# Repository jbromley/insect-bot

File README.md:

Insect Bot README
=================

This repository contains code and other documents for an insect bot based on
the bot in chapter 4 of [Make: Arduino Bots and Gadgets: Six Embedded
Projects with Open Source Hardware and
Software](http://www.amazon.com/Make-Embedded-Projects-Hardware-Discovery/dp/1449389716/ref=sr_1_1?ie=UTF8&qid=1329163647&sr=8-1).

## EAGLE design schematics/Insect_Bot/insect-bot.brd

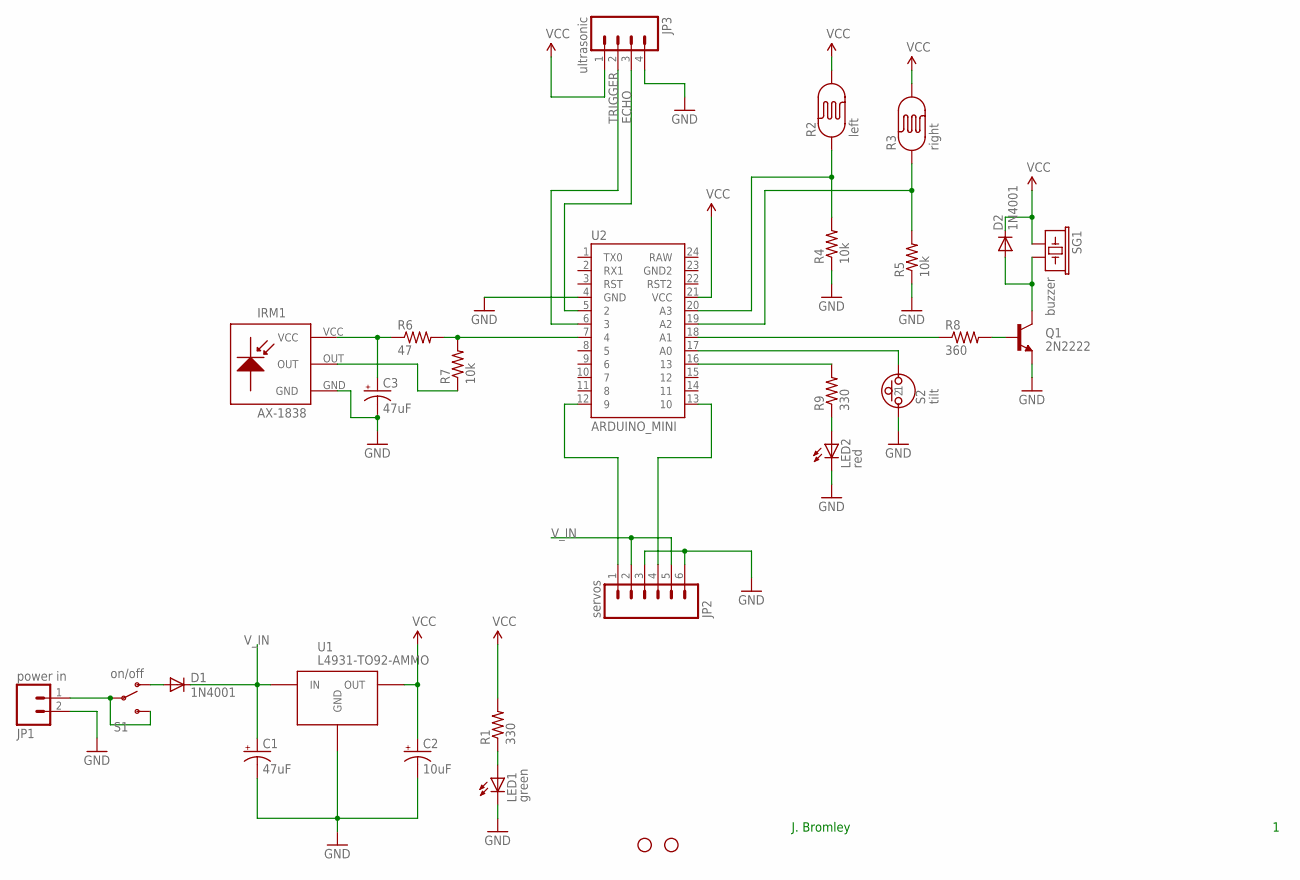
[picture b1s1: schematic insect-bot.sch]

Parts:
C1: 47uF; CPOL-RADIAL-10UF-25V
C2: 10uF; CPOL-RADIAL-10UF-25V
C3: 47uF; CPOL-RADIAL-100UF-25V
D1, D2: 1N4001; DIODE-1N4001
IRM1: AX-1838
JP1: power in; 1X02
JP2: servos; 1X06
JP3: ultrasonic; 1X04
JP4, JP5: STAND-OFF
LED1: green; LED3MM
LED2: red; LED3MM
Q1: 2N2222; TO-92-AMMO
R1, R9: 330; AXIAL-0.3
R2: left; PHOTOCELL
R3: right; PHOTOCELL
R4, R5, R7: 10k; AXIAL-0.3
R6: 47; AXIAL-0.3
R8: 360; AXIAL-0.3
S1: on/off; SWITCH-SPDT
S2: tilt; RADIAL-100
SG1: buzzer; BUZZER-12MM
U1: L4931-TO92-AMMO; TO-92-AMMO
U2: ARDUINO_MINI

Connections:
ECHO: JP3.3, U2.5 (2)
GND: C1.2 (-), C2.2 (-), C3.2 (-), IRM1.GND, JP1.2, JP2.3, JP2.6, JP3.4, LED1.K (C), LED2.K (C), Q1.1 (E), R4.P$1 (1), R5.P$1 (1), S2.1, U1.2 (GND), U2.4 (GND)
unnamed: JP1.1, S1.2, S1.3 (S)
unnamed: D1.A, S1.1 (O)
unnamed: LED1.A, R1.P$1 (1)
unnamed: JP2.1, U2.12 (9)
unnamed: JP2.4, U2.13 (10)
unnamed: R8.P$1 (1), U2.18 (A1)
unnamed: R3.1, R5.P$2 (2), U2.19 (A2)
unnamed: R2.1, R4.P$2 (2), U2.20 (A3)
unnamed: R6.P$2 (2), R7.P$2 (2), U2.7 (4)
unnamed: Q1.2 (B), R8.P$2 (2)
unnamed: D2.A, Q1.3 (C), SG1.- (2)
unnamed: S2.2, U2.17 (A0)
unnamed: R9.P$2 (2), U2.16 (13)
unnamed: LED2.A, R9.P$1 (1)
REMOTE: IRM1.OUT, R7.P$1 (1)
TRIGGER: JP3.2, U2.6 (3)
VCC: C2.1 (+), C3.1 (+), D2.C, IRM1.VCC, JP3.1, R1.P$2 (2), R2.2, R3.2, R6.P$1 (1), SG1.+ (1), U1.3 (OUT), U2.21 (VCC)
V_IN: C1.1 (+), D1.C, JP2.2, JP2.5, U1.1 (IN)

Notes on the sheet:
J. Bromley

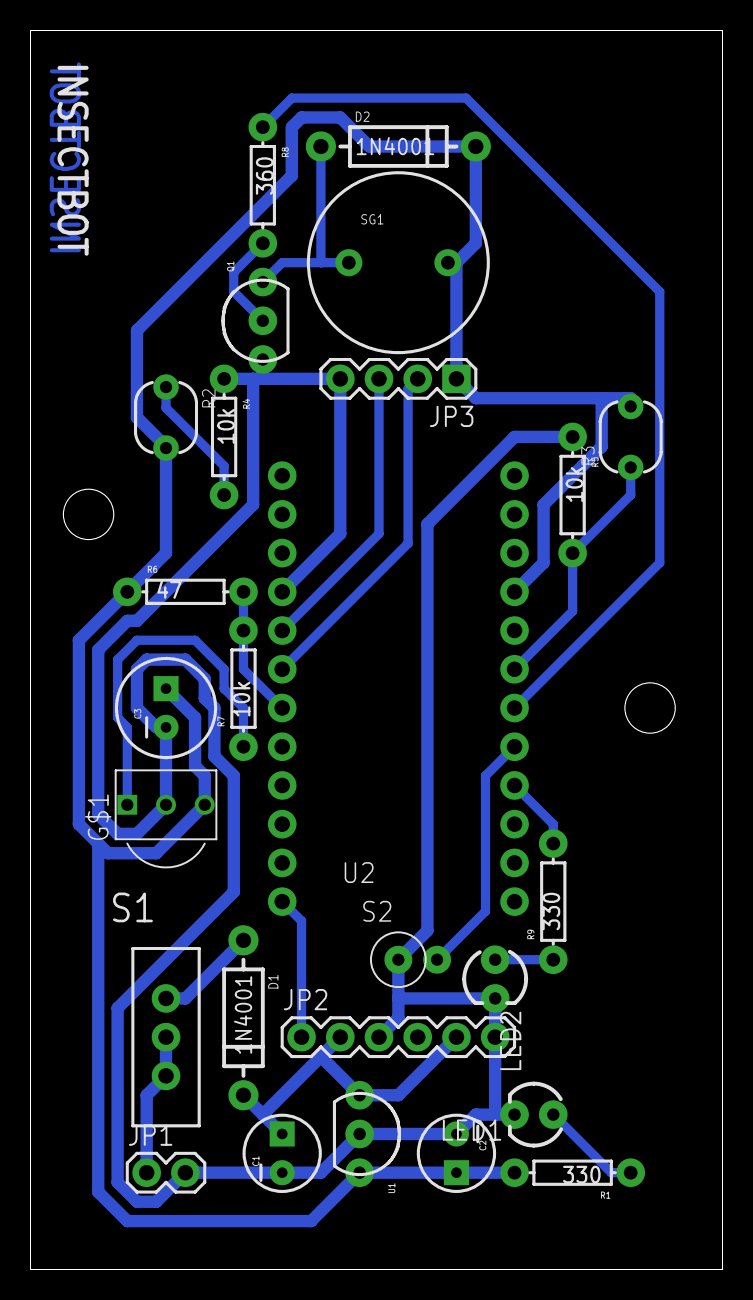
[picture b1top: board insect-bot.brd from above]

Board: 2 copper layers, 45.4 x 81.3 mm, 28 parts (0 on the bottom side), 20 nets.

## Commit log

2012-02-15 First commit.
2012-02-15 Renamed README to use markdown.
2012-02-22 Added ideas, outcomes, and preliminary plan.
    Added a description of the desired outcome. Brainstormed for robot
    ideas. Made a plan for walking tasks.
2012-02-22 Added servo centering and walking sketches.
    Added a sketch that moves the servo with a potentiometer to figure
    out where the center point is. Added a sketch to test the walking
    behaviors.
2012-02-22 Modified gait code.
    Define gaits as offsets from zero. Reduce all movement to a move
    function with a parameter that tells the kind of motion.
2012-02-24 Added planning.
    Added planning for walking, ultrasonic sensor, and light reaction.
2012-02-24 Made sketch work both front and rear legs.
    Adjusted the sketch to move both the front and rear legs. The legs
    are moved in opposite directions.
2012-02-24 Added tasks to plan.
2012-02-24 Added .gitignore.
    Make git ignore all files in sketch build directories.
2012-02-24 Added backup files to .gitignore.
2012-02-24 Added minicom config.
    Added a configuration to be able to talk to the Arduino serial port
    using minicom.
2012-02-25 Added power circuit schematic.
    Added a schematic for a power circuit. I can construct a smaller
    version that should work for the bot.
2012-02-25 Begin power board design.
    Added a Fritzing project with the power board design. Updated
    project plan for power board progress.
2012-02-25 Initial layout of power board.
    Did an initial layout of the power board. Checked in changes before
    attempting a more compact layout.
2012-02-25 Did a layout for a double-sided power board.
2012-02-27 Laid out circuit.
    Changed the layout of the circuit to be produced on a two-sided board.
2012-02-27 Modified plan for power and traction problems.
    I will need to make some changes to better run off of a 9V battery.
    I also need to get better traction from the feet.
2012-02-28 Added light sensor and ultrasonic tasks.
    Added tasks to test ultrasonic sensor response and a simple two
    photoresistor set up for light avoidance/seeking behavior.
2012-03-09 Modified gait and added photoresistor test.
    Modified the center points of the gait and added a time scaler to be
    able to scale how fast the bot walks. Added a photoresistor test to
    see if and how well two photoresistors can give information about
    where light is coming from.
2012-03-13 Added ultrasonic sensor and tilt switch.
    Added ultrasonic sensor to measure distance and two distance
    indicator LEDs. Added a tilt switch with tilt LED indicator.
2012-03-13 Updated plan progress.
    Added progress on the light-sensing circuit and tilt switch detector.
2012-03-15 Added Fritzing project for circuit design.
    Added a Fritzing project that fully describes the bot's circuitry.
    Also added Fritzing components for the HC-SR04 and the IR receiver.
2012-03-15 Added datasheets for the HC-SR04 and IR receiver.
2012-03-16 Added IR receiver to Fritzing design project.
2012-03-16 Added remote control to the walking test.
    Allow an IR remote control to control the direction the bot walks
    and stop the bot.
2012-03-16 Added remote codes file.
    Added a file that details the codes sent for each button on the
    Car MP3 remote control.
2012-03-16 Completed circuit design.
2012-03-17 Rewired the IR receiver.
    Rewired the IR receiver to use the circuit recommended in the data
    sheet for the AX-1383HS. This required adding two resistors and a
    capacitor.
2012-03-17 Added .DS_Store files to git ignore file.
2012-03-17 Added gschem symbol for the Arduino Pro Mini.
2012-03-18 Tweaks to Arduino Pro Mini.
    Added labels for the PWM pins. Removed the sch file -- symbols must
    use the extension "sym".
2012-03-18 Added symbol for the IR receiver.
    Added a symbol for the AX-1838HS IR receiver. Included both the
    tragesym source file and the generated symbol.
2012-03-18 Added Arduino Pro Mini generated symbol.
2012-03-21 Cleaned up circuit board.
    Added a custom symbol for the AX-1838HS ultrasonic sensor. General
    cleanup of the PCB.
2012-03-26 Added data sheet for the piezo buzzer.
2012-03-27 Initial version of EAGLE design files.
    I have switched from GEDA to EAGLE. These are the first iteration
    of the EAGLE design files.
2012-03-28 Added a git ignore file.
2012-03-28 Added *.pro to git ignore file.
2012-03-29 First completed insect bot PCB.
    First revision with poured-copper ground plane.
2012-03-29 Fixed some traces that were too near each other.
2012-03-29 Finished board layout.
    Spaced out close traces. Added a ground plane.
2012-04-06 Made traces thicker.
    Upped power net traces to 32 mil with 16 mil clearance and signal
    net traces to 24 mil with 16 mil clearance.
2012-04-11 Final layout for insect bot board.
    Made traces a bit wider. Increased size of pad for the IR remote
    receiver.
2012-04-13 Added drill file information to documentation.
    Added a spreadsheet of drill sizes and locations. Added a graphic
    showing drill hole sizes and positions.
2012-04-26 Updated plan.
    Updated completed tasks related to the board build. Added plan items
    for testing all components on the board.
2012-05-07 Updated circuit debugging process.
2012-05-07 Added circuit test code.
    Added code that will individually test each of the sensors and
    actuators.
2012-05-09 Added IR remote test program.
    Added a test program that simply receives commands and outputs the
    corresponding key press to serial out.
2012-05-25 Added MP3 remote control documentation.
    Added a document that contains the code generated by each key on
    the MP3 remote control.

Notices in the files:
parts and their libraries:
SparkFun-Boards: Licensing: CC v3.0 Share-Alike You are welcome to use this library for commercial purposes.
SparkFun-Aesthetics: Released under the Creative Commons
SparkFun-Aesthetics: http://creativecommons.org/licenses/by-sa/3.0
